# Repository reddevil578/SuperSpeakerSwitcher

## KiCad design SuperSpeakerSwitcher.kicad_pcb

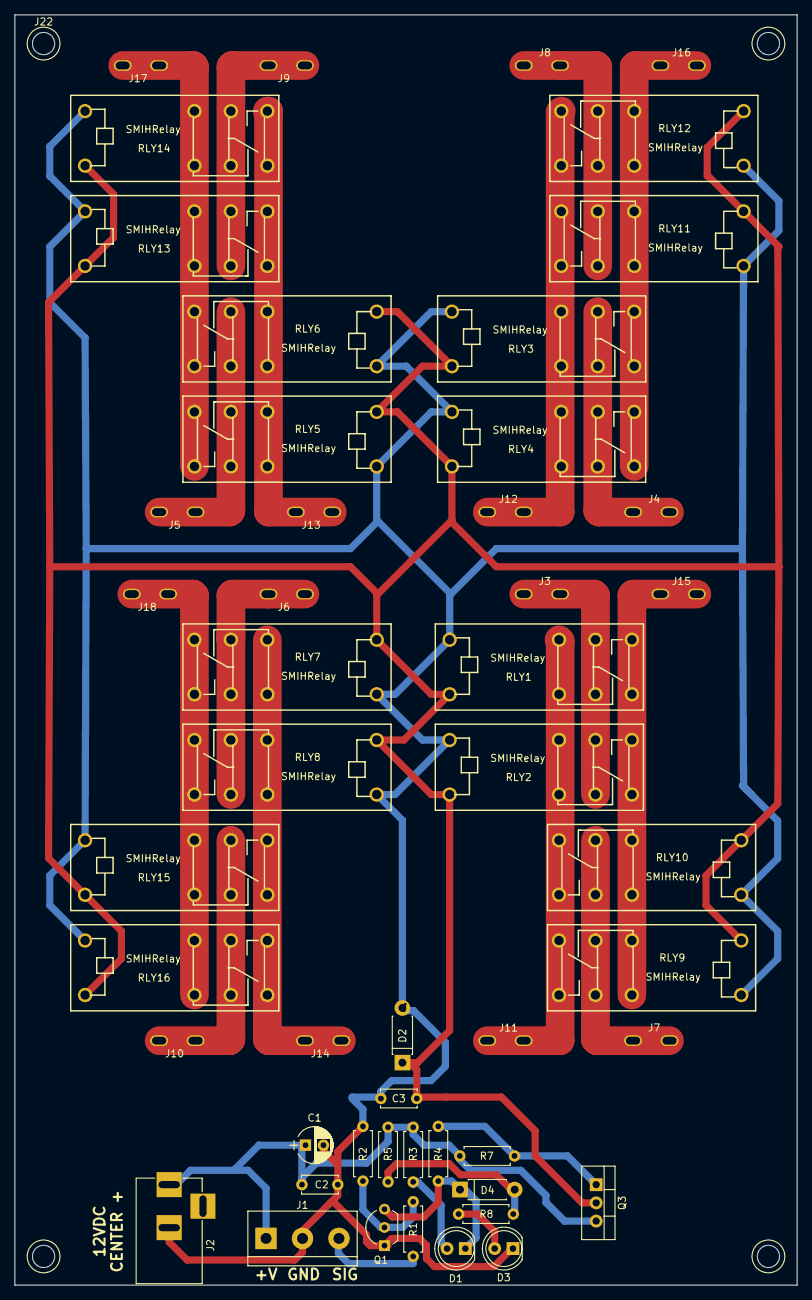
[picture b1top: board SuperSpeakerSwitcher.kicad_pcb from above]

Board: 2 copper layers, 109.0 x 177.0 mm, 54 parts (0 on the bottom side), 25 nets.

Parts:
C1: 10 uF; CP_Radial_D5.0mm_P2.50mm
C2, C3: 100 nF; C_Disc_D5.0mm_W2.5mm_P5.00mm
D1, D3: LED; LED_D5.0mm
D2, D4: 1N4007; D_DO-41_SOD81_P7.62mm_Horizontal
J1: Conn_01x03; TerminalBlock_bornier-3_P5.08mm
J2: Jack-DC; BARREL_JACK
J3, J4, J5, J6, J7, J8, J9, J10, J11, J12, J13, J14, J15, J16, J17, J18: Conn_01x01; SpadeTerminal635
J19, J20, J21, J22: Conn_01x01; 1pin
Q1: 2N3904; TO-92_Inline_Wide
Q3: TIP127; TO-220-3_Vertical
R1: 10k; R_Axial_DIN0207_L6.3mm_D2.5mm_P7.62mm_Horizontal
R2, R7: 100k; R_Axial_DIN0207_L6.3mm_D2.5mm_P7.62mm_Horizontal
R3: 2k2; R_Axial_DIN0207_L6.3mm_D2.5mm_P7.62mm_Horizontal
R4, R5, R8: 1k; R_Axial_DIN0207_L6.3mm_D2.5mm_P7.62mm_Horizontal
RLY1, RLY2, RLY3, RLY4, RLY5, RLY6, RLY7, RLY8, RLY9, RLY10, RLY11, RLY12, RLY13, RLY14, RLY15, RLY16: SPDTRelay; SMIHRelay

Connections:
+12V: C1.1, C2.1, J1.1, J2.1, Q3.3, R3.1, R5.1, R7.1
AMP1SPK1NEG: J4.1, RLY3.1, RLY4.1
AMP1SPK1POS: J3.1, RLY1.1, RLY2.1
AMP1SPK2NEG: J6.1, RLY7.1, RLY8.1
AMP1SPK2POS: J5.1, RLY5.1, RLY6.1
AMP2SPK1NEG: J8.1, RLY11.1, RLY12.1
AMP2SPK1POS: J7.1, RLY9.1, RLY10.1
AMP2SPK2NEG: J10.1, RLY15.1, RLY16.1
AMP2SPK2POS: J9.1, RLY13.1, RLY14.1
COILV: C3.1, D2.1, Q3.2, RLY1.5, RLY2.5, RLY3.5, RLY4.5, RLY5.5, RLY6.5, RLY7.5, RLY8.5, RLY9.5, RLY10.5, RLY11.5, RLY12.5, RLY13.5, RLY14.5, RLY15.5, RLY16.5
GND: C1.2, C2.2, C3.2, D2.2, D3.1, J1.2, J2.2, Q1.1, R2.2, RLY1.4, RLY2.4, RLY3.4, RLY4.4, RLY5.4, RLY6.4, RLY7.4, RLY8.4, RLY9.4, RLY10.4, RLY11.4, RLY12.4, RLY13.4, RLY14.4, RLY15.4, RLY16.4
unnamed: D1.1, D4.1, Q1.3, R4.1
unnamed: D1.2, R3.2
unnamed: D3.2, R8.2
unnamed: D4.2, R5.2, R8.1
unnamed: Q1.2, R1.2, R2.1
unnamed: Q3.1, R4.2, R7.2
OUT1SPK1NEG: J12.1, RLY3.2, RLY4.2, RLY11.3, RLY12.3
OUT1SPK1POS: J11.1, RLY1.2, RLY2.2, RLY9.3, RLY10.3
OUT1SPK2NEG: J14.1, RLY7.2, RLY8.2, RLY15.3, RLY16.3
OUT1SPK2POS: J13.1, RLY5.2, RLY6.2, RLY13.3, RLY14.3
OUT2SPK1NEG: J16.1, RLY3.3, RLY4.3, RLY11.2, RLY12.2
OUT2SPK1POS: J15.1, RLY1.3, RLY2.3, RLY9.2, RLY10.2
OUT2SPK2NEG: J18.1, RLY7.3, RLY8.3, RLY15.2, RLY16.2
OUT2SPK2POS: J17.1, RLY5.3, RLY6.3, RLY13.2, RLY14.2

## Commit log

2020-12-26 Alternate routing
2020-12-26 Remove erroneous diodes
